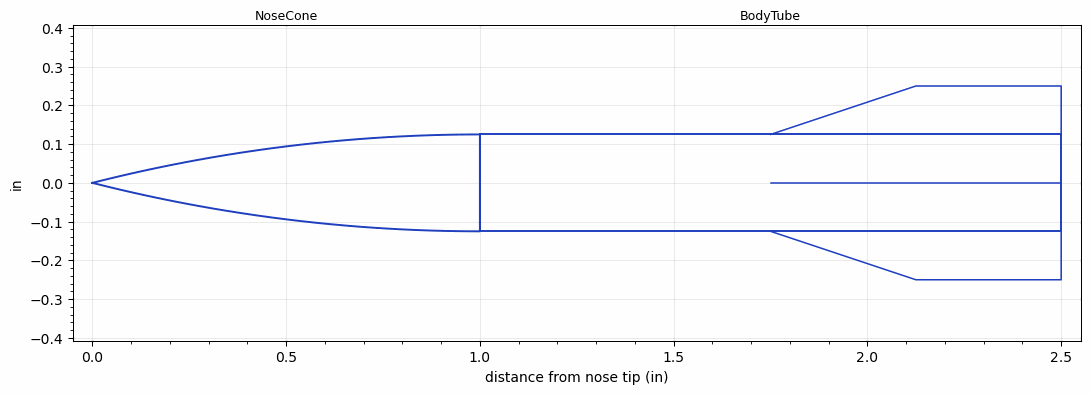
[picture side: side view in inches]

<RASAeroDocument>
 <FileVersion>2</FileVersion>
 <RocketDesign>
  <NoseCone>
   <Length>1</Length>
   <Diameter>0.25</Diameter>
   <Shape>Tangent Ogive</Shape>
   <Location>0</Location>
  </NoseCone>
  <BodyTube>
   <Length>1.5</Length>
   <Diameter>0.25</Diameter>
   <Location>1</Location>
   <Fin>
    <Count>4</Count>
    <Chord>0.75</Chord>
    <Span>0.125</Span>
    <SweepDistance>0.375</SweepDistance>
    <TipChord>0.375</TipChord>
    <Thickness>0.0225</Thickness>
    <Location>0.75</Location>
    <AirfoilSection>Hexagonal Blunt Base</AirfoilSection>
    <FX1>0.189</FX1>
    <FX3>0.189</FX3>
   </Fin>
  </BodyTube>
  <Surface>Smooth (Zero Roughness)</Surface>
  <ModifiedBarrowman>False</ModifiedBarrowman>
  <Turbulence>False</Turbulence>
  <UseBooster1>False</UseBooster1>
  <UseBooster2>False</UseBooster2>
 </RocketDesign>
 <LaunchSite>
  <Altitude>0</Altitude>
  <Pressure>0</Pressure>
  <RodAngle>0</RodAngle>
  <RodLength>4</RodLength>
  <Temperature>74</Temperature>
  <WindSpeed>0</WindSpeed>
 </LaunchSite>
 <Recovery>
  <Altitude1>1000</Altitude1>
  <Altitude2>1000</Altitude2>
  <DeviceType1>None</DeviceType1>
  <DeviceType2>None</DeviceType2>
  <Event1>False</Event1>
  <Event2>False</Event2>
  <Size1>1</Size1>
  <Size2>1</Size2>
  <EventType1>None</EventType1>
  <EventType2>None</EventType2>
  <CD1>1.33</CD1>
  <CD2>1.33</CD2>
 </Recovery>
 <MachAlt>
  <Item>0, 0</Item>
  <Item>2.5, 0</Item>
  <Item>5, 4750</Item>
  <Item>10, 0</Item>
  <Item>25, 0</Item>
 </MachAlt>
</RASAeroDocument>
